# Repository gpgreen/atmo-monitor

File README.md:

# atmo-monitor

KiCad design for a atmospheric measurement board. The MCU is a
stm32f103cbt6. There are 2 main sensors. One is the PMS2007, which
measures particulates, ie PM2.5. The other sensor is a BME680, which
measures temperature, pressure, and organic compounds. The
measurements are output on an E-Ink tri-color display.

This design is a continuation of a project that I did using a nucleo dev board
and a perfboard pcb. The main goals used for this design:

    - Use smd devices that I had already for the project, instead of a dev board
    - Use an [Adafruit power supply breakout](https://www.adafruit.com/product/1944) that allows the use of a lithium battery. I didn't
    want to implement this on the PCB for this project, and I don't have those types of devices on hand.
    - Hand soldering for the pcb instead of my usual hot-plate reflow technique. This means
    using 1206 size components instead of 0603, and SO footprint parts. This also helps with
    the previous goal of using parts I had already, as my newer designs use TQFP footprints. I have successfully
    hand soldered the smaller parts, but it is very tedious.

I was able to finish the design using those goals and the only part I needed to purchase was the adafruit power breakout. It
is a 2-layer PCB that I have shared at [Oshpark](https://oshpark.com/shared_projects/oVsTK2Hw).

## Changes

- Rev A
  Original

## Firmware

[Firmware](https://github.com/gpgreen/atmo-monitor-stm32)

## Connections to Segger JTAG

I have put test points on the board, so that pogo pins can be used to program
the MCU.

[jlink web page](https://www.segger.com/products/debug-probes/j-link/technology/interface-description/)
```
**** 20 Pin connector for JTAG
                -------
    VTref      1|*   *|2 NC
    nTRST      3|*   *|4 GND
    TDI        5|*   *|6 GND
    TMS        7|*   *|8 GND
    TCK        9|*   *|10 GND
    RTCK      11|*   *|12 GND
    TDO       13|*   *|14 GND
    RESET     15|*   *|16 GND*
    DBGRQ     17|*   *|18 GND*
    5V Supply 19|*   *|20 GND*
                -------
```
From a 20pin JTAG connector, run wires to the following test pads to connect a debugger:
```
VTRef 1  <-> 3V3
SWDIO 7  <-> SWD
SWCLK 9  <-> SWC
RESET 15 <-> RST
GND   4  <-> GND
```

## Running SEGGER JLink

Run the JLink GDB server via the following:
```
JLinkGDBServer -if SWD -device STM32F103CB
```

GDB can be connected via the following:
```
gdb-multiarch --command=jlink-stm32.gdb target/thumbv7m/debug/main
```

## Running ocd
```
openocd -f interface/stlink-v3.cfg -f target/stm32f1x.cfg
```

## Credits

as always, thanks for the good work
- [Adafruit](https://www.adafruit.com)

## License

Licensed under

- MIT license ([LICENSE-MIT](LICENSE-MIT) or http://opensource.org/licenses/MIT)

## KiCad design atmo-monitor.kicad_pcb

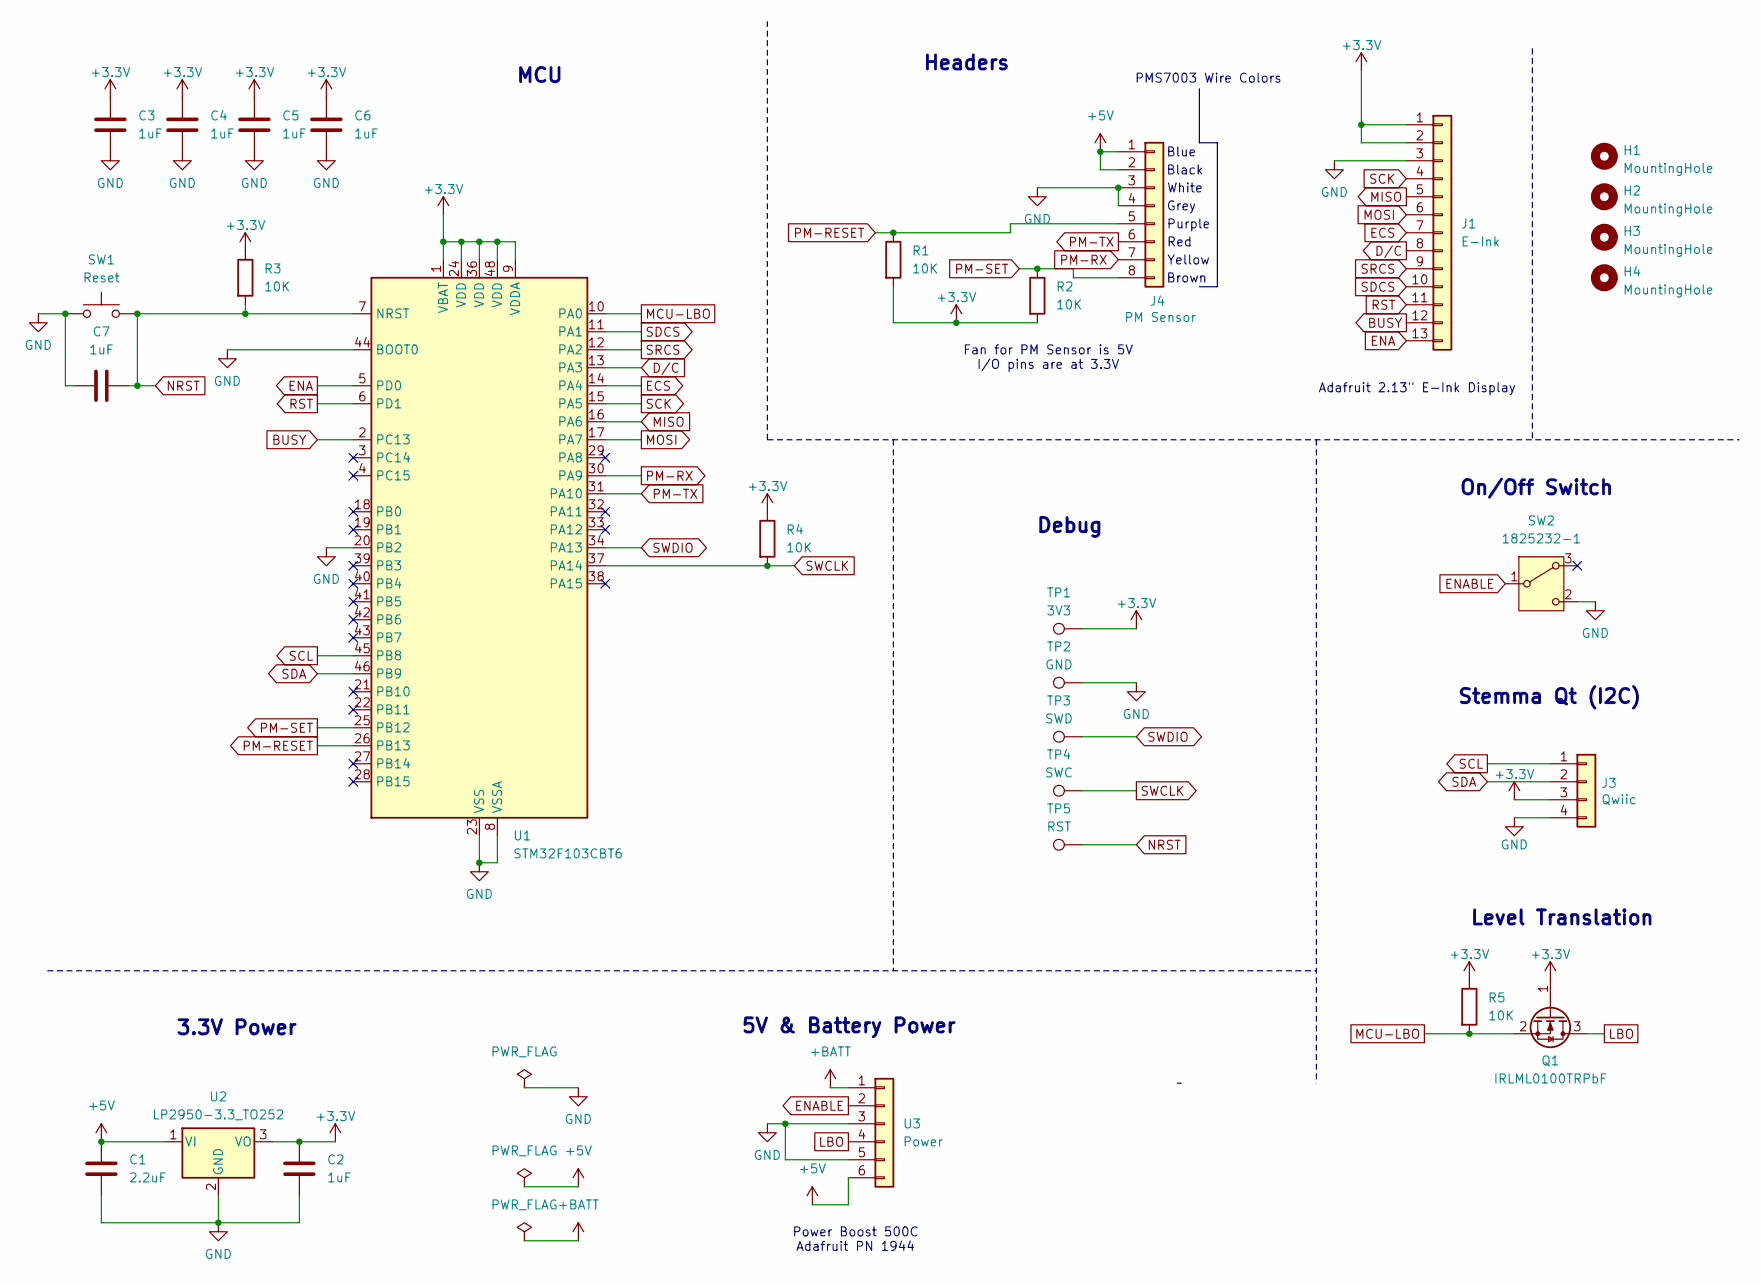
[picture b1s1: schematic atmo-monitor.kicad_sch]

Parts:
C1: 2.2uF; C_1206_3216Metric_Pad1.33x1.80mm_HandSolder
C2, C3, C4, C5, C6, C7: 1uF; C_1206_3216Metric_Pad1.33x1.80mm_HandSolder
H1, H2, H3, H4: MountingHole; MountingHole_2.5mm_Pad
J1: E-Ink; PinHeader_1x13_P2.54mm_Vertical
J3: Qwiic; JST_SH_BM04B-SRSS-TB_1x04-1MP_P1.00mm_Vertical
J4: PM Sensor; JST_PH_B8B-PH-K_1x08_P2.00mm_Vertical
Q1: IRLML0100TRPbF; SOT-23
R1, R2, R3, R4, R5: 10K; R_1206_3216Metric_Pad1.30x1.75mm_HandSolder
SW1: Reset; OnShine KPT-1187B
SW2: 1825232-1; TE-1825232-1
TP1: 3V3; TestPoint_Pad_D2.0mm
TP2: GND; TestPoint_Pad_D2.0mm
TP3: SWD; TestPoint_Pad_D2.0mm
TP4: SWC; TestPoint_Pad_D2.0mm
TP5: RST; TestPoint_Pad_D2.0mm
U1: STM32F103CBT6; LQFP-48_7x7mm_P0.5mm
U2: LP2950-3.3_TO252; TO-252-2
U3: Power; Adafruit Powerboost 500+

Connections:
+3.3V: C2.1, C3.1, C4.1, C5.1, C6.1, J1.1, J1.2, J3.3, Q1.1 (G), R1.2, R2.2, R3.1, R4.1, R5.1, TP1.1, U1.1 (VBAT), U1.9 (VDDA), U1.24 (VDD), U1.36 (VDD), U1.48 (VDD), U2.3 (VO)
+5V: C1.1, J4.1, J4.2, U2.1 (VI), U3.6
+BATT: U3.1
BUSY: J1.12, U1.2 (PC13)
D/C: J1.8, U1.13 (PA3)
ECS: J1.7, U1.14 (PA4)
ENA: J1.13, U1.5 (PD0)
ENABLE: SW2.1 (B), U3.2
GND: C1.2, C2.2, C3.2, C4.2, C5.2, C6.2, C7.2, J1.3, J3.4, J4.3, J4.4, SW1.1, SW2.2 (C), TP2.1, U1.8 (VSSA), U1.20 (PB2), U1.23 (VSS), U1.35 (VSS), U1.44 (BOOT0), U1.47 (VSS), U2.2 (GND), U3.3, U3.5
LBO: Q1.3 (D), U3.4
MCU-LBO: Q1.2 (S), R5.2, U1.10 (PA0)
MISO: J1.5, U1.16 (PA6)
MOSI: J1.6, U1.17 (PA7)
NRST: C7.1, R3.2, SW1.2, TP5.1, U1.7 (NRST)
PM-RESET: J4.5, R1.1, U1.26 (PB13)
PM-RX: J4.7, U1.30 (PA9)
PM-SET: J4.8, R2.1, U1.25 (PB12)
PM-TX: J4.6, U1.31 (PA10)
RST: J1.11, U1.6 (PD1)
SCK: J1.4, U1.15 (PA5)
SCL: J3.1, U1.45 (PB8)
SDA: J3.2, U1.46 (PB9)
SDCS: J1.10, U1.11 (PA1)
SRCS: J1.9, U1.12 (PA2)
SWCLK: R4.2, TP4.1, U1.37 (PA14)
SWDIO: TP3.1, U1.34 (PA13)

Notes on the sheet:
Black
3.3V Power
Headers
PMS7003 Wire Colors
Power Boost 500C Adafruit PN 1944
Debug
MCU
Grey
Red
Yellow
Adafruit 2.13" E-Ink Display
Purple
Level Translation
Fan for PM Sensor is 5V I/O pins are at 3.3V
White
Stemma Qt (I2C)
Blue
On/Off Switch
Brown
5V & Battery Power

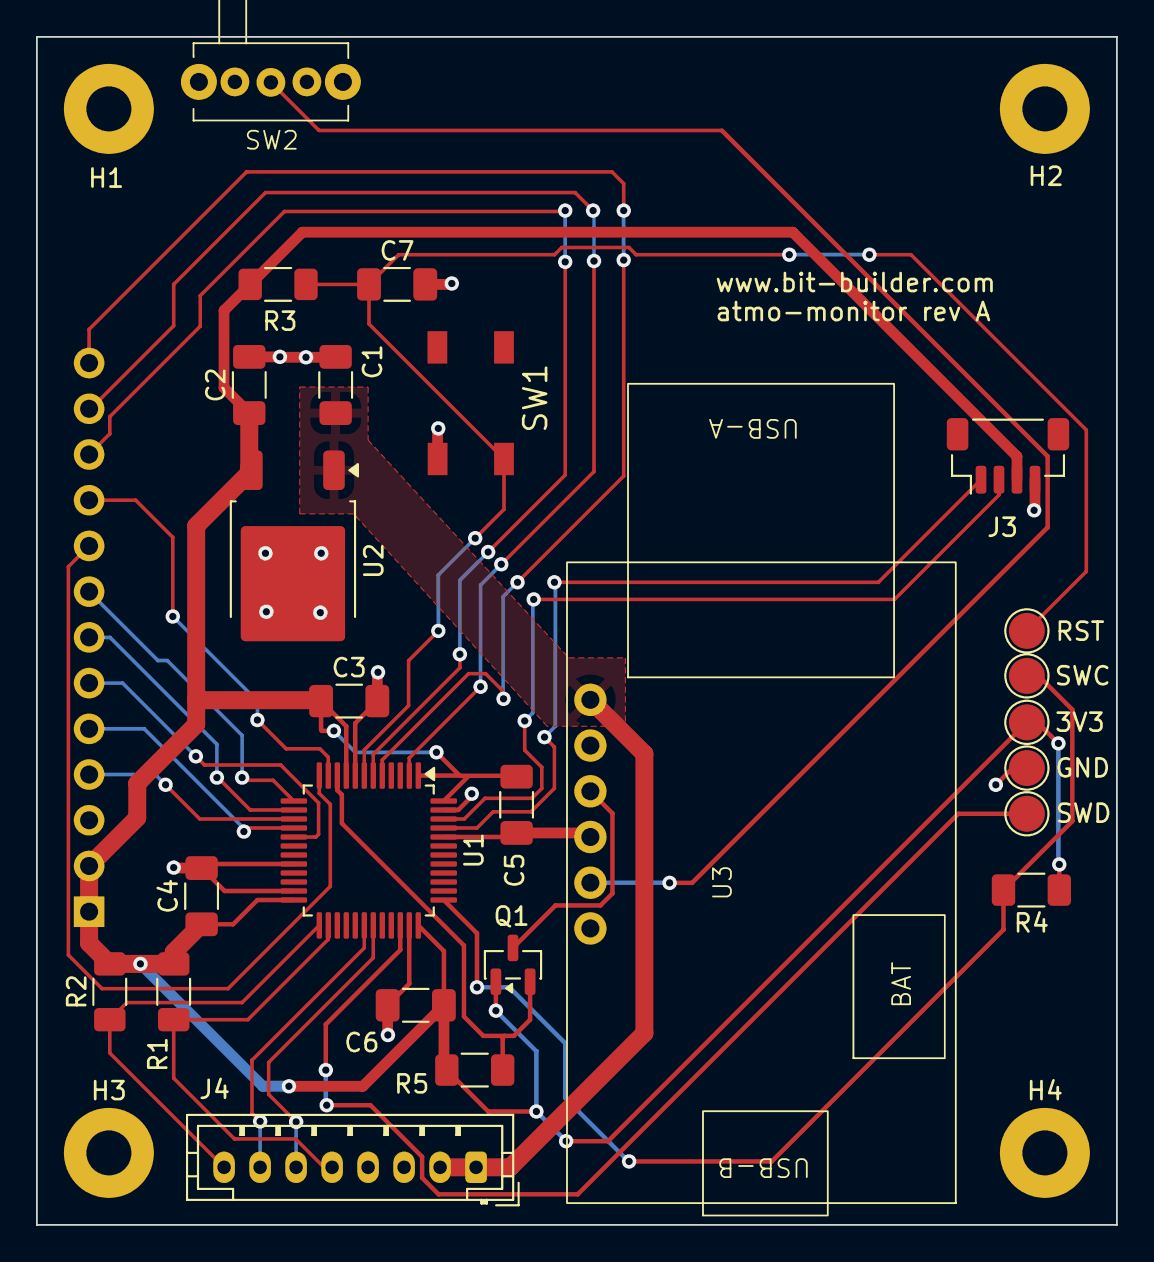
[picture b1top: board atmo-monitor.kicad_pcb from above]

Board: 2 copper layers, 60.0 x 66.0 mm, 30 parts (1 on the bottom side), 25 nets.

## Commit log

2025-10-28 Finished initial design
2025-10-30 Moved 2 signals from output limited ports
2025-10-30 Added OshPark board link
    Updated readme a bit
2025-10-30 Added R4 for SWCLK
    Reordered debug test points
    Fixed schematic DRC problems
2025-10-30 Added R5 for LBO pull up on MCU
    For proper level translation, need R5
    Swapped RX and TX on PMS jumper so that it is legibly correct
2025-10-30 Updated trace routing for better clearance
2025-10-30 Finished schematic drc checks
    Update pdb from schematic, no real changes
2025-10-30 Updated oshpark link
2025-10-30 Updated drawing blocks for rev A tagging
